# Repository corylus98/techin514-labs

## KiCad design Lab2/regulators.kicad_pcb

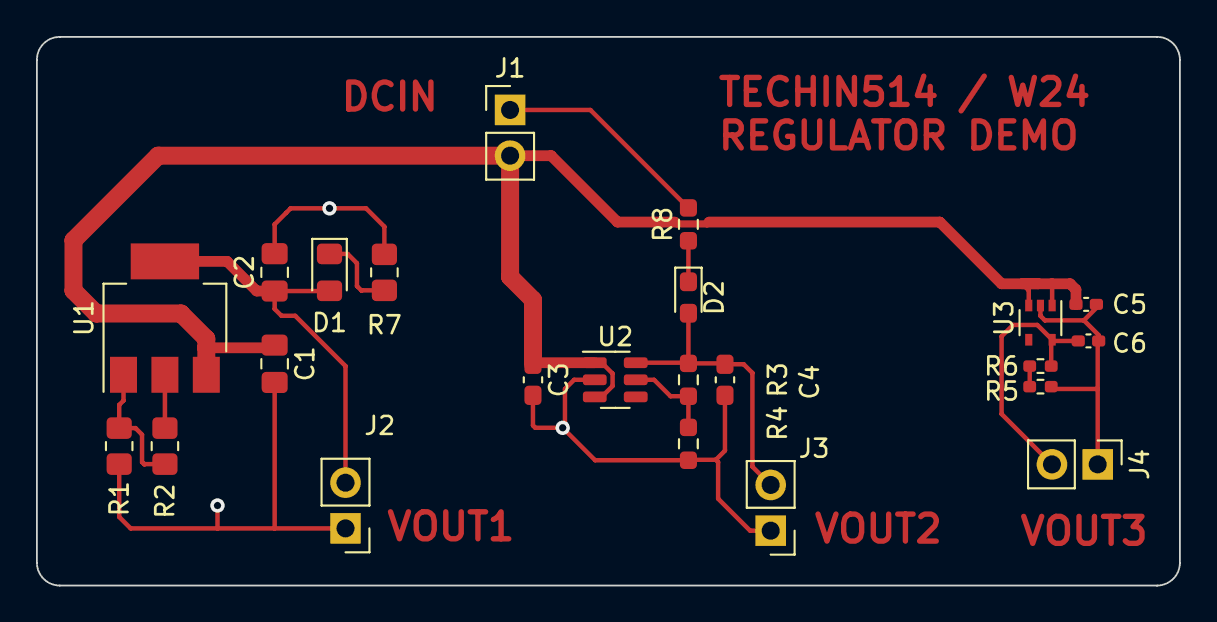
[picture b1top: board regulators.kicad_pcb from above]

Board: 2 copper layers, 63.5 x 30.5 mm, 23 parts (0 on the bottom side), 10 nets.

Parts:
C1, C2: 1uF; C_0805_2012Metric_Pad1.18x1.45mm_HandSolder
C3, C4: 1uF; C_0603_1608Metric_Pad1.08x0.95mm_HandSolder
C5, C6: 1uF; C_0402_1005Metric_Pad0.74x0.62mm_HandSolder
D1: LED; LED_0805_2012Metric_Pad1.15x1.40mm_HandSolder
D2: LED; LED_0603_1608Metric_Pad1.05x0.95mm_HandSolder
J1, J2, J3, J4: n.m.; PinHeader_1x02_P2.54mm_Vertical
R1, R2, R7: R; R_0805_2012Metric_Pad1.20x1.40mm_HandSolder
R3, R4, R8: R; R_0603_1608Metric_Pad0.98x0.95mm_HandSolder
R5, R6: R; R_0402_1005Metric_Pad0.72x0.64mm_HandSolder
U1: LM317_SOT-223; SOT-223-3_TabPin2
U2: TPS79301-EP; SOT-23-6
U3: MIC5366-3.3YC5; SOT-353_SC-70-5

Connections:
+VDC: C1.1, C3.1, C5.2, J1.2, U1.3 (VI), U2.1 (IN), U2.3 (EN), U3.1 (VIN), U3.3 (EN)
GND: C1.2, C2.2, C3.2, C4.2, C5.1, C6.2, J1.1, J2.1, J3.1, J4.1, R1.2, R4.2, R6.2, R7.2, R8.2, U2.2 (GND), U3.2 (GND)
unnamed: C2.1, D1.2 (A), J2.2, R2.2, U1.2 (VO)
unnamed: D1.1 (K), R7.1
unnamed: C4.1, D2.2 (A), J3.2, R3.1, U2.6 (OUT)
unnamed: D2.1 (K), R8.1
unnamed: C6.1, J4.2, R5.1, U3.5 (VOUT)
unnamed: R5.2, R6.1
unnamed: R1.1, R2.1, U1.1 (ADJ)
unnamed: R3.2, R4.1, U2.5 (FB)

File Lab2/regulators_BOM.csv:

Reference,Value,Datasheet,Footprint,Qty,DNP
"C1,C2,C3,C4,C5,C6",1uF,~,-- mixed values --,6,
D1,LS R976,~,LED_SMD:LED_0805_2012Metric_Pad1.15x1.40mm_HandSolder,1,
D2,LTST-C191KRKT,~,LED_SMD:LED_0603_1608Metric_Pad1.05x0.95mm_HandSolder,1,
"J1,J2,J3,J4",n.m.,~,Connector_PinHeader_2.54mm:PinHeader_1x02_P2.54mm_Vertical,4,
R1,270K Ohm,~,Resistor_SMD:R_0805_2012Metric_Pad1.20x1.40mm_HandSolder,1,
R2,430K Ohm,~,Resistor_SMD:R_0805_2012Metric_Pad1.20x1.40mm_HandSolder,1,
R3,360K Ohm,~,Resistor_SMD:R_0603_1608Metric_Pad0.98x0.95mm_HandSolder,1,
R4,470K Ohm,~,Resistor_SMD:R_0603_1608Metric_Pad0.98x0.95mm_HandSolder,1,
R5,750K Ohm,~,Resistor_SMD:R_0402_1005Metric_Pad0.72x0.64mm_HandSolder,1,
R6,680K Ohm,~,Resistor_SMD:R_0402_1005Metric_Pad0.72x0.64mm_HandSolder,1,
R7,1.5 Ohm,~,Resistor_SMD:R_0805_2012Metric_Pad1.20x1.40mm_HandSolder,1,
R8,4.3 Ohm,~,Resistor_SMD:R_0603_1608Metric_Pad0.98x0.95mm_HandSolder,1,
U1,LM317_SOT-223,http://www.ti.com/lit/ds/symlink/lm317.pdf,Package_TO_SOT_SMD:SOT-223-3_TabPin2,1,
U2,TPS79301-EP,http://www.ti.com/lit/ds/symlink/tps79333-ep.pdf,Package_TO_SOT_SMD:SOT-23-6,1,
U3,MIC5377,http://ww1.microchip.com/downloads/en/DeviceDoc/mic5365.pdf,Package_TO_SOT_SMD:SOT-353_SC-70-5,1,

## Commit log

2025-02-03 Create Labs Folder
2025-02-03 Remove key
2025-02-03 Create folder for all labs
2025-02-06 Add files for Lab 4
